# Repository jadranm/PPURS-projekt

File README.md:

# PPURS-projekt

CO₂ alarm baziran na ATmega platformi sa Senseair S8 LP senzorom. 
<br>Mikrokontroler ATmega 32 koristeći PWM izlaz senzora s kojima pomoću pinova za vanjske prekide izračunava koncentraciju ugljikovog dioksida u zraku. Uređaj ispisuje izmjerenu koncentraciju CO₂ na vanjskom LCD 16x2 displeju.

Projekt je napravljen za kolegij Projektiranje i primjena ugradbenih računalnih sustava (PPURS).
<br>Programirano u Atmel studiu a PCB je dizajniran u KiCadu.
__________________________________________________________________________________________________________________________________________________________________________

    TVZ prijediplomski elektrotehnika / Projektiranje i primjena ugradbenih računalnih sustava 
    [PPURS] 2022/2023 6. semestar

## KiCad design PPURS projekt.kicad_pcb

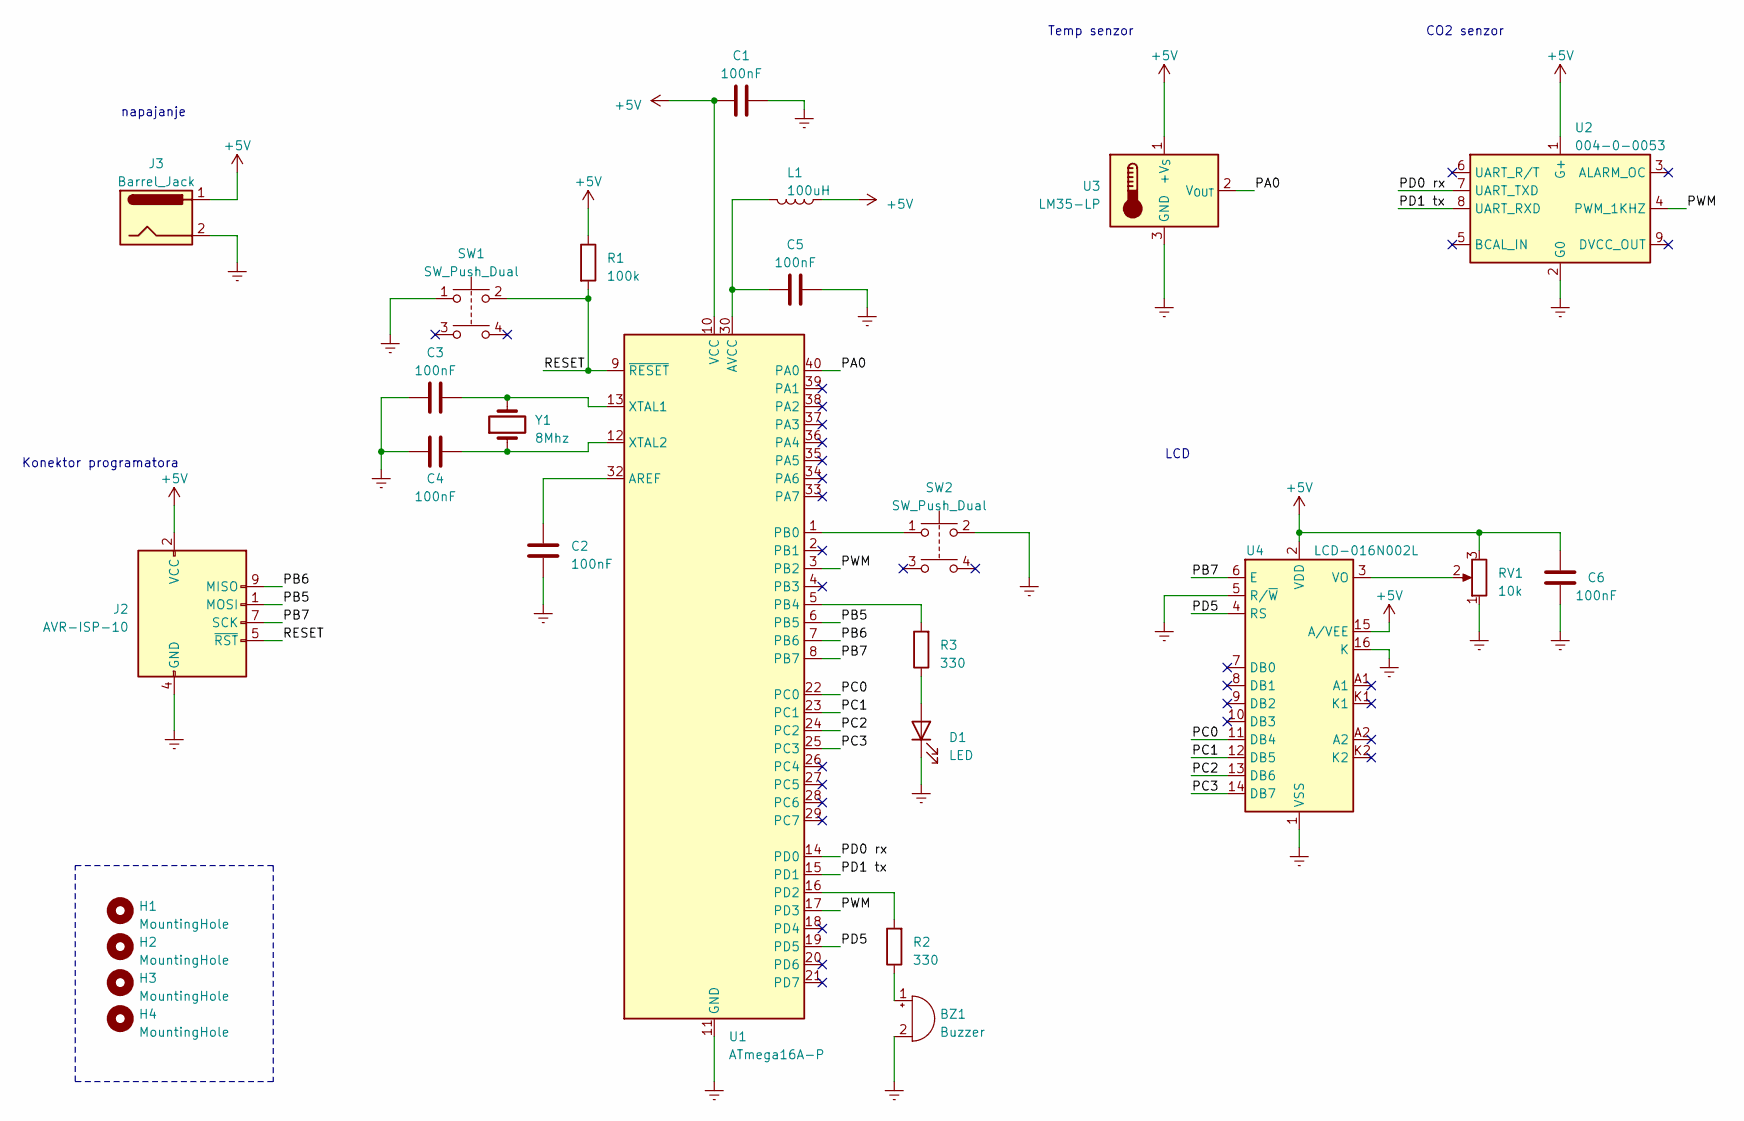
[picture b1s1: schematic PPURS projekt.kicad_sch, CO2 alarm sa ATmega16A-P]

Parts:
BZ1: Buzzer; Buzzer_12x9.5RM7.6
C1, C2, C3, C4, C5, C6: 100nF; CP_Radial_Tantal_D5.0mm_P5.00mmJM
D1: LED; LED_D5.0mm_Clear
H1, H2, H3, H4: MountingHole; MountingHole_3.2mm_M3_ISO7380_Pad_TopBottom
J2: AVR-ISP-10; IDC-Header_2x05_P2.54mm_Vertical
J3: Barrel_Jack; BarrelJack_CUI_PJ-063AH_HorizontalJM
L1: 100uH; L_Axial_L5.3mm_D2.2mm_P10.16mm_Horizontal_Vishay_IM-1
R1: 100k; R_Axial_DIN0309_L9.0mm_D3.2mm_P12.70mm_Horizontal
R2, R3: 330; R_Axial_DIN0309_L9.0mm_D3.2mm_P12.70mm_Horizontal
RV1: 10k; Potentiometer_Piher_PT-15-V02_Vertical
SW1, SW2: SW_Push_Dual; SW_PUSH_6mm_H7.3mm
U1: ATmega16A-P; DIP-40_W15.24mm
U2: 004-0-0053; Senseair_S8_Down
U3: LM35-LP; TO-92_Inline
U4: LCD-016N002L; PinHeader_2x08_P2.54mm_Verticaljm
Y1: 8Mhz; Crystal_HC49-4H_Vertical

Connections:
+5V: C1.1, C6.1, J2.2 (VCC), J3.1, L1.1, R1.1, RV1.3, U1.10 (VCC), U2.1 (G+), U3.1 (+V_{S}), U4.2 (VDD), U4.15 (A/VEE)
/PA0: U1.40 (PA0), U3.2 (V_{OUT})
/PB5: J2.1 (MOSI), U1.6 (PB5)
/PB6: J2.9 (MISO), U1.7 (PB6)
/PB7: J2.7 (SCK), U1.8 (PB7), U4.6 (E)
/PC0: U1.22 (PC0), U4.11 (DB4)
/PC1: U1.23 (PC1), U4.12 (DB5)
/PC2: U1.24 (PC2), U4.13 (DB6)
/PC3: U1.25 (PC3), U4.14 (DB7)
/PD0 rx: U1.14 (PD0), U2.7 (UART_TXD)
/PD1 tx: U1.15 (PD1), U2.8 (UART_RXD)
/PD5: U1.19 (PD5), U4.4 (RS)
/PWM: U1.3 (PB2), U1.17 (PD3), U2.4 (PWM_1KHZ)
/RESET: J2.5 (~RST), R1.2, SW1.2, U1.9 (~RESET)
Earth: BZ1.2 (+), C1.2, C2.1, C3.2, C4.2, C5.1, C6.2, D1.1 (K), J2.4 (GND), J2.6 (GND), J2.8 (GND), J2.10 (GND), J3.2, RV1.1, SW1.1, SW2.2, U1.11 (GND), U1.31 (GND), U2.2 (G0), U3.3 (GND), U4.1 (VSS), U4.5 (R/~W), U4.16 (K)
unnamed: BZ1.1 (-), R2.1
unnamed: D1.2 (A), R3.1
unnamed: C2.2, U1.32 (AREF)
unnamed: C5.2, L1.2, U1.30 (AVCC)
unnamed: SW2.1, U1.1 (PB0)
unnamed: R3.2, U1.5 (PB4)
unnamed: R2.2, U1.16 (PD2)
unnamed: C3.1, U1.13 (XTAL1), Y1.2
unnamed: C4.1, U1.12 (XTAL2), Y1.1
unnamed: RV1.2, U4.3 (VO)

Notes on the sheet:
CO2 senzor
Temp senzor
LCD
napajanje
Konektor programatora

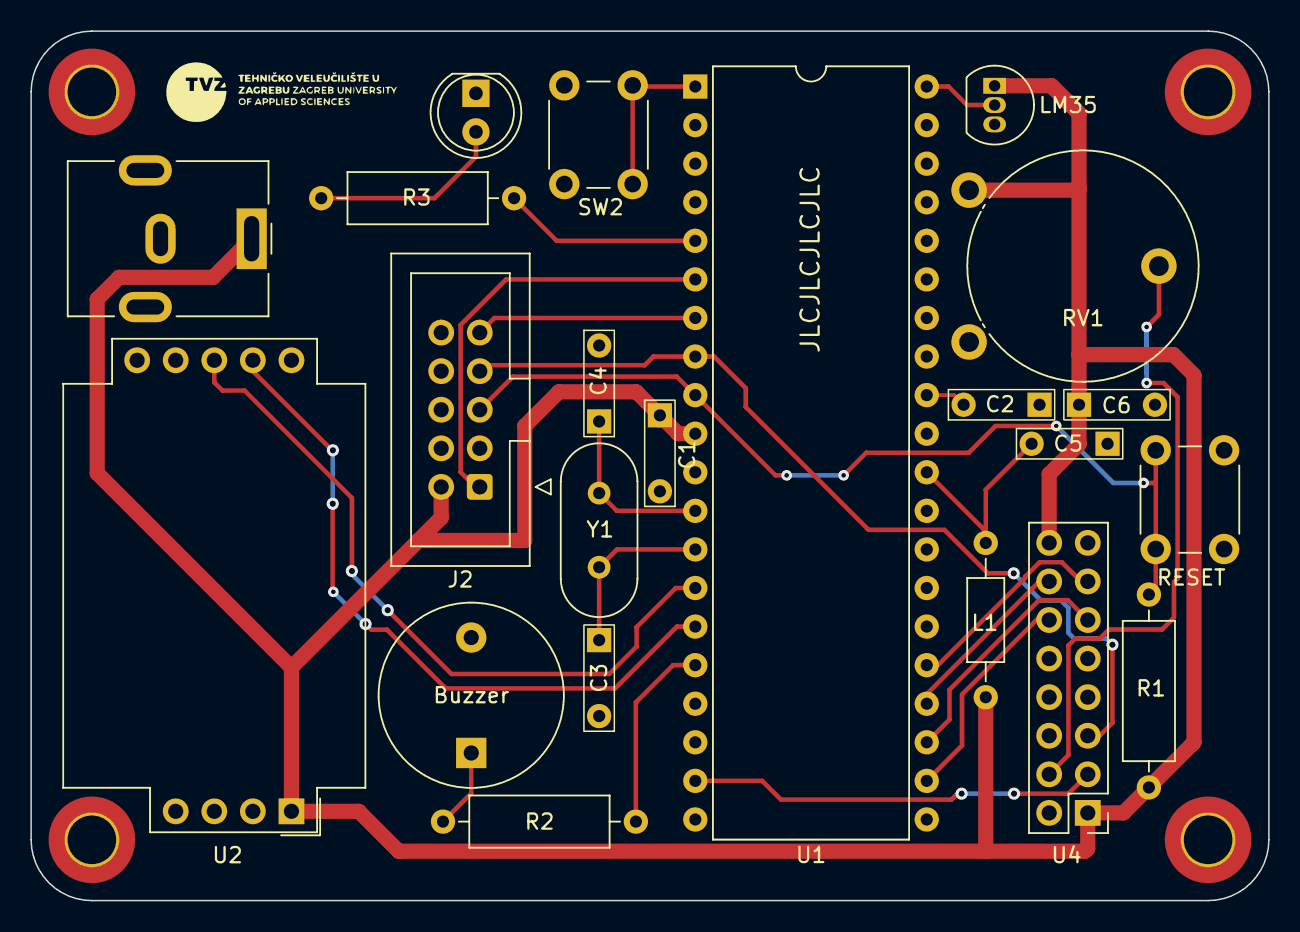
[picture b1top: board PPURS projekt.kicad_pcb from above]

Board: 2 copper layers, 81.5 x 57.2 mm, 26 parts (0 on the bottom side), 25 nets.

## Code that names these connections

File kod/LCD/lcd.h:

/*
 Naslov: MIKRORAÈUNALA - Programiranje mikrokontrolera porodice
 Atmel u programskom okruenju Atmel Studio 6
 Autori: Zoran Vrhovski, Marko Miletiæ
 
 lcd.h
 
 */ 

#include <avr/io.h>
#include <stdio.h>
#include <string.h>
#include <avr/pgmspace.h>
#include <util/delay.h>
#include "../AVR lib/AVR_lib.h"

// konfiguracija LCD displeja
#define LCD_DATA0_PORT   PORTC     	// port za 4 bitnu komunikaciju - podatkovni bit 0 	//D4
#define LCD_DATA1_PORT   PORTC     	// port za 4 bitnu komunikaciju - podatkovni bit 1 	//D5
#define LCD_DATA2_PORT   PORTC     	// port za 4 bitnu komunikaciju - podatkovni bit 2 	//D6
#define LCD_DATA3_PORT   PORTC     	// port za 4 bitnu komunikaciju - podatkovni bit 3 	//D7
#define LCD_DATA0_PIN    PC0          // pin za 4 bitnu komunikaciju - podatkovni bit 0 //D4
#define LCD_DATA1_PIN    PC1          // pin za 4 bitnu komunikaciju - podatkovni bit 1 //D5
#define LCD_DATA2_PIN    PC2          // pin za 4 bitnu komunikaciju - podatkovni bit 2 //D6
#define LCD_DATA3_PIN    PC3          // pin za 4 bitnu komunikaciju - podatkovni bit 3 //D7
#define LCD_RS_PORT      PORTD     	// port za odabir registra //RS
#define LCD_RS_PIN       PD5          // pin  za odabir registra
#define LCD_E_PORT       PORTB    	// port za odobrenje upisa //EN
#define LCD_E_PIN        PB7          // port za odobrenje upisa								//izmjenjeno PD7 na PB7

#define LCD_LINES		2			// broj vidljivih linija na LCD displeju
#define LCD_DISP_LENGTH  16    		// broj vidljivih znakova po liniji na LCD displeju

//#define LCD_RW_PORT      LCD_PORT // port za  èitanje/pisanje - mi samo piemo //RW
//#define LCD_RW_PIN       5        // pin za  èitanje/pisanje - mi samo piemo

// kraj konfiguracije LCD displeja




// instruction register bit positions, see HD44780U datasheet
#define LCD_CLR               	0x0    	// DB0: clear display
#define LCD_HOME              	0x1    	// DB1: return to home position
#define LCD_ENTRY_MODE        	0x2     // DB2: set entry mode
#define LCD_ENTRY_INC         	0x1     // DB1: 1=increment, 0=decrement
#define LCD_ENTRY_SHIFT       	0x0     // DB2: 1=display shift on
#define LCD_ON                	0x3     // DB3: turn lcd/cursor on
#define LCD_ON_DISPLAY        	0x2     // DB2: turn display on
#define LCD_ON_CURSOR         	0x1     // DB1: turn cursor on
#define LCD_ON_BLINK          	0x0     // DB0: blinking cursor ?
#define LCD_MOVE              	0x4     // DB4: move cursor/display
#define LCD_MOVE_DISP         	0x3     // DB3: move display (0-> cursor) ?
#define LCD_MOVE_RIGHT        	0x2     // DB2: move right (0-> left) ?
#define LCD_FUNCTION          	0x5     // DB5: function set
#define LCD_FUNCTION_8BIT     	0x4     // DB4: set 8BIT mode (0->4BIT mode)
#define LCD_FUNCTION_2LINES   	0x3     // DB3: two lines (0->one line)
#define LCD_FUNCTION_10DOTS   	0x2     // DB2: 5x10 font (0->5x7 font)
#define LCD_CGRAM             	0x6     // DB6: set CG RAM address
#define LCD_DDRAM             	0x7     // DB7: set DD RAM address
#define LCD_BUSY              	0x7     // DB7: LCD is busy

// set entry mode: display shift on/off, dec/inc cursor move direction
#define LCD_ENTRY_DEC            0x04	// display shift off, dec cursor move dir
#define LCD_ENTRY_DEC_SHIFT      0x05   // display shift on,  dec cursor move dir
#define LCD_ENTRY_INC_           0x06   // display shift off, inc cursor move dir
#define LCD_ENTRY_INC_SHIFT      0x07   // display shift on,  inc cursor move dir

// display on/off, cursor on/off, blinking char at cursor position
#define LCD_DISP_OFF             0x08   // display off
#define LCD_DISP_ON              0x0C   // display on, cursor off
#define LCD_DISP_ON_BLINK        0x0D   // display on, cursor off, blink char
#define LCD_DISP_ON_CURSOR       0x0E   // display on, cursor on
#define LCD_DISP_ON_CURSOR_BLINK 0x0F   // display on, cursor on, blink char

// move cursor/shift display
#define LCD_MOVE_CURSOR_LEFT     0x10   // move cursor left  (decrement)
#define LCD_MOVE_CURSOR_RIGHT    0x14   // move cursor right (increment)
#define LCD_MOVE_DISP_LEFT       0x18   // shift display left
#define LCD_MOVE_DISP_RIGHT      0x1C   // shift display right

// function set: set interface data length and number of display lines
#define LCD_FUNCTION_4BIT_1LINE  0x20   // 4-bit interface, single line, 5x7 dots
#define LCD_FUNCTION_4BIT_2LINES 0x38   // 4-bit interface, dual line,   5x7 dots
#define LCD_FUNCTION_8BIT_1LINE  0x30   // 8-bit interface, single line, 5x7 dots
#define LCD_FUNCTION_8BIT_2LINES 0x38   // 8-bit interface, dual line,   5x7 dots

#define LCD_START_LINE1  		 0x00   // DDRAM address of first char of line 1
#define LCD_START_LINE2  		 0x40   // DDRAM address of first char of line 2
#define LCD_START_LINE3  		 0x14   // DDRAM address of first char of line 3
#define LCD_START_LINE4  		 0x54   // DDRAM address of first char of line 4



// --- LCD Utils
// functional macros
#define lcd_e_delay()   __asm__ __volatile__( "rjmp 1f\n 1:" );
#define lcd_e_high()    LCD_E_PORT  |=  _BV(LCD_E_PIN);
#define lcd_e_low()     LCD_E_PORT  &= ~_BV(LCD_E_PIN);
#define lcd_rs_high()   LCD_RS_PORT |=  _BV(LCD_RS_PIN)
#define lcd_rs_low()    LCD_RS_PORT &= ~_BV(LCD_RS_PIN)
// address of data direction register of port x
#define LCD_DDR(x) 		(*(&x - 1))





// --- Forward functions


//-----------------------------------------------------------------------------------------
// FUNCTION: _auxToggleE
// PURPOSE: flush channel E
void lcd_e_toggle(void);

//-----------------------------------------------------------------------------------------
// FUNCTION: lcd_write
// PURPOSE: send a character or an instruction to the LCD
void lcd_write(uint8_t data,uint8_t rs) ;

//-----------------------------------------------------------------------------------------
// FUNCTION: lcd_instr
// PURPOSE:  send an instruction to the LCD
void lcd_instr(uint8_t instr);

//-----------------------------------------------------------------------------------------
// FUNCTION: lcd_char
// PURPOSE:  send a character to the LCD
void lcd_char(uint8_t data);

//-----------------------------------------------------------------------------------------
// FUNCTION: lcd_init
// PURPOSE:  Initialize LCD to 4 bit I/O mode
void lcd_init();

//-----------------------------------------------------------------------------------------
// FUNCTION: lcd_newline
// PURPOSE:  Move cursor on specified line
void lcd_setline(uint8_t line);

extern int g_nCurrentLine;

//-----------------------------------------------------------------------------------------
// FUNCTION: lcd_print
// PURPOSE:  send a null terminated string to the LCD eg. char x[10]="hello!";
void lcd_print2(char *text);
void lcd_print(char *szFormat, ...);

//-----------------------------------------------------------------------------------------
// FUNCTION: lcd_gotoxy
// PURPOSE:  Set cursor to specified position
//           Input:    x  row (0 -> first row)
//                     y  column (0 -> first column)
void lcd_gotoxy(uint8_t x, uint8_t y);

//-----------------------------------------------------------------------------------------
// FUNCTION: lcd_clrscr
// PURPOSE:  Clear display and set cursor to home position
void lcd_clrscr(void);

//-----------------------------------------------------------------------------------------
// FUNCTION: lcd_home
// PURPOSE:  Set cursor to home position
void lcd_home(void);
//-----------------------------------------------------------------------------------------
// FUNCTION: lcd_define_char
// PURPOSE:  set additional characters in CGRAM
void lcd_define_char(void);

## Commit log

2023-05-12 Add files via upload
    prvi upload
2023-06-08 dodavanje koda
2023-06-08 komentari
2023-06-09 dodan ADC za LM35
2023-06-09 maknute fileovi koji su visak
2023-06-09 maknuti fileovi koji su visak
2023-06-11 Uart
2023-06-20 dokumenti
2023-06-27 pwm radi
2023-07-05 finalni kod
